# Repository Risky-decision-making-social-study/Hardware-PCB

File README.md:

# rpi-header-pcb

BOM: <https://risky-decision-making-social-study.github.io/Hardware-PCB/>

## Kicad project

The kicad project situated in the `monkey-rpi-header-pcb/` folder.

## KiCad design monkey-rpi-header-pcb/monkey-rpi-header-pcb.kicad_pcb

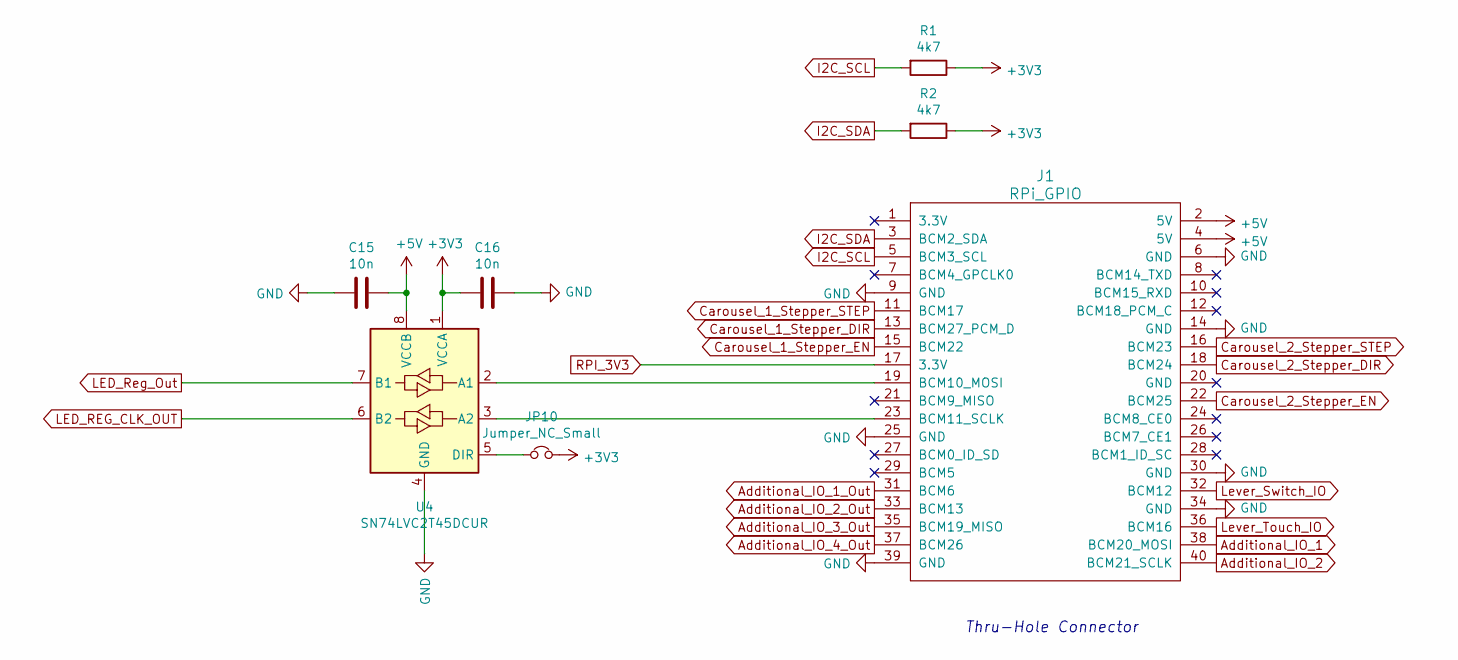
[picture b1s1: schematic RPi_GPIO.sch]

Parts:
C15, C16: 10n; C_0603_1608Metric; Part CL10B103KB8NNNC
J1: RPi_GPIO; Pin_Header_Straight_2x20; Part PRT-14017
JP10: Jumper_NC_Small; SolderJumper-2_P1.3mm_Bridged_RoundedPad1.0x1.5mm
R1, R2: 4k7; R_0805_2012Metric; Part CRCW08054K70FKEAC
U4: SN74LVC2T45DCUR; VSSOP-8_2.4x2.1mm_P0.5mm

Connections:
+5V: C15.1, J1.2 (5V), J1.4 (5V), U4.8 (VCCB); also elsewhere on the board
Additional_IO_1: J1.38 (BCM20_MOSI); also elsewhere on the board
Additional_IO_1_Out: J1.31 (BCM6); also elsewhere on the board
Additional_IO_2: J1.40 (BCM21_SCLK); also elsewhere on the board
Additional_IO_2_Out: J1.33 (BCM13); also elsewhere on the board
Additional_IO_3_Out: J1.35 (BCM19_MISO); also elsewhere on the board
Additional_IO_4_Out: J1.37 (BCM26); also elsewhere on the board
Carousel_1_Stepper_DIR: J1.13 (BCM27_PCM_D); also elsewhere on the board
Carousel_1_Stepper_EN: J1.15 (BCM22); also elsewhere on the board
Carousel_1_Stepper_STEP: J1.11 (BCM17); also elsewhere on the board
Carousel_2_Stepper_DIR: J1.18 (BCM24); also elsewhere on the board
Carousel_2_Stepper_EN: J1.22 (BCM25); also elsewhere on the board
Carousel_2_Stepper_STEP: J1.16 (BCM23); also elsewhere on the board
GND: C15.2, C16.1, J1.6 (GND), J1.9 (GND), J1.14 (GND), J1.25 (GND), J1.30 (GND), J1.34 (GND), J1.39 (GND), U4.4 (GND); also elsewhere on the board
I2C_SCL: J1.5 (BCM3_SCL), R1.2; also elsewhere on the board
I2C_SDA: J1.3 (BCM2_SDA), R2.2; also elsewhere on the board
LED_REG_CLK_OUT: U4.6 (B2); also elsewhere on the board
LED_Reg_Out: U4.7 (B1); also elsewhere on the board
Lever_Switch_IO: J1.32 (BCM12); also elsewhere on the board
Lever_Touch_IO: J1.36 (BCM16); also elsewhere on the board
unnamed: J1.19 (BCM10_MOSI), U4.2 (A1)
unnamed: J1.23 (BCM11_SCLK), U4.3 (A2)
unnamed: JP10.1, U4.5 (DIR)
RPI_3V3: J1.17 (3.3V); also elsewhere on the board

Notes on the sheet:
Thru-Hole Connector

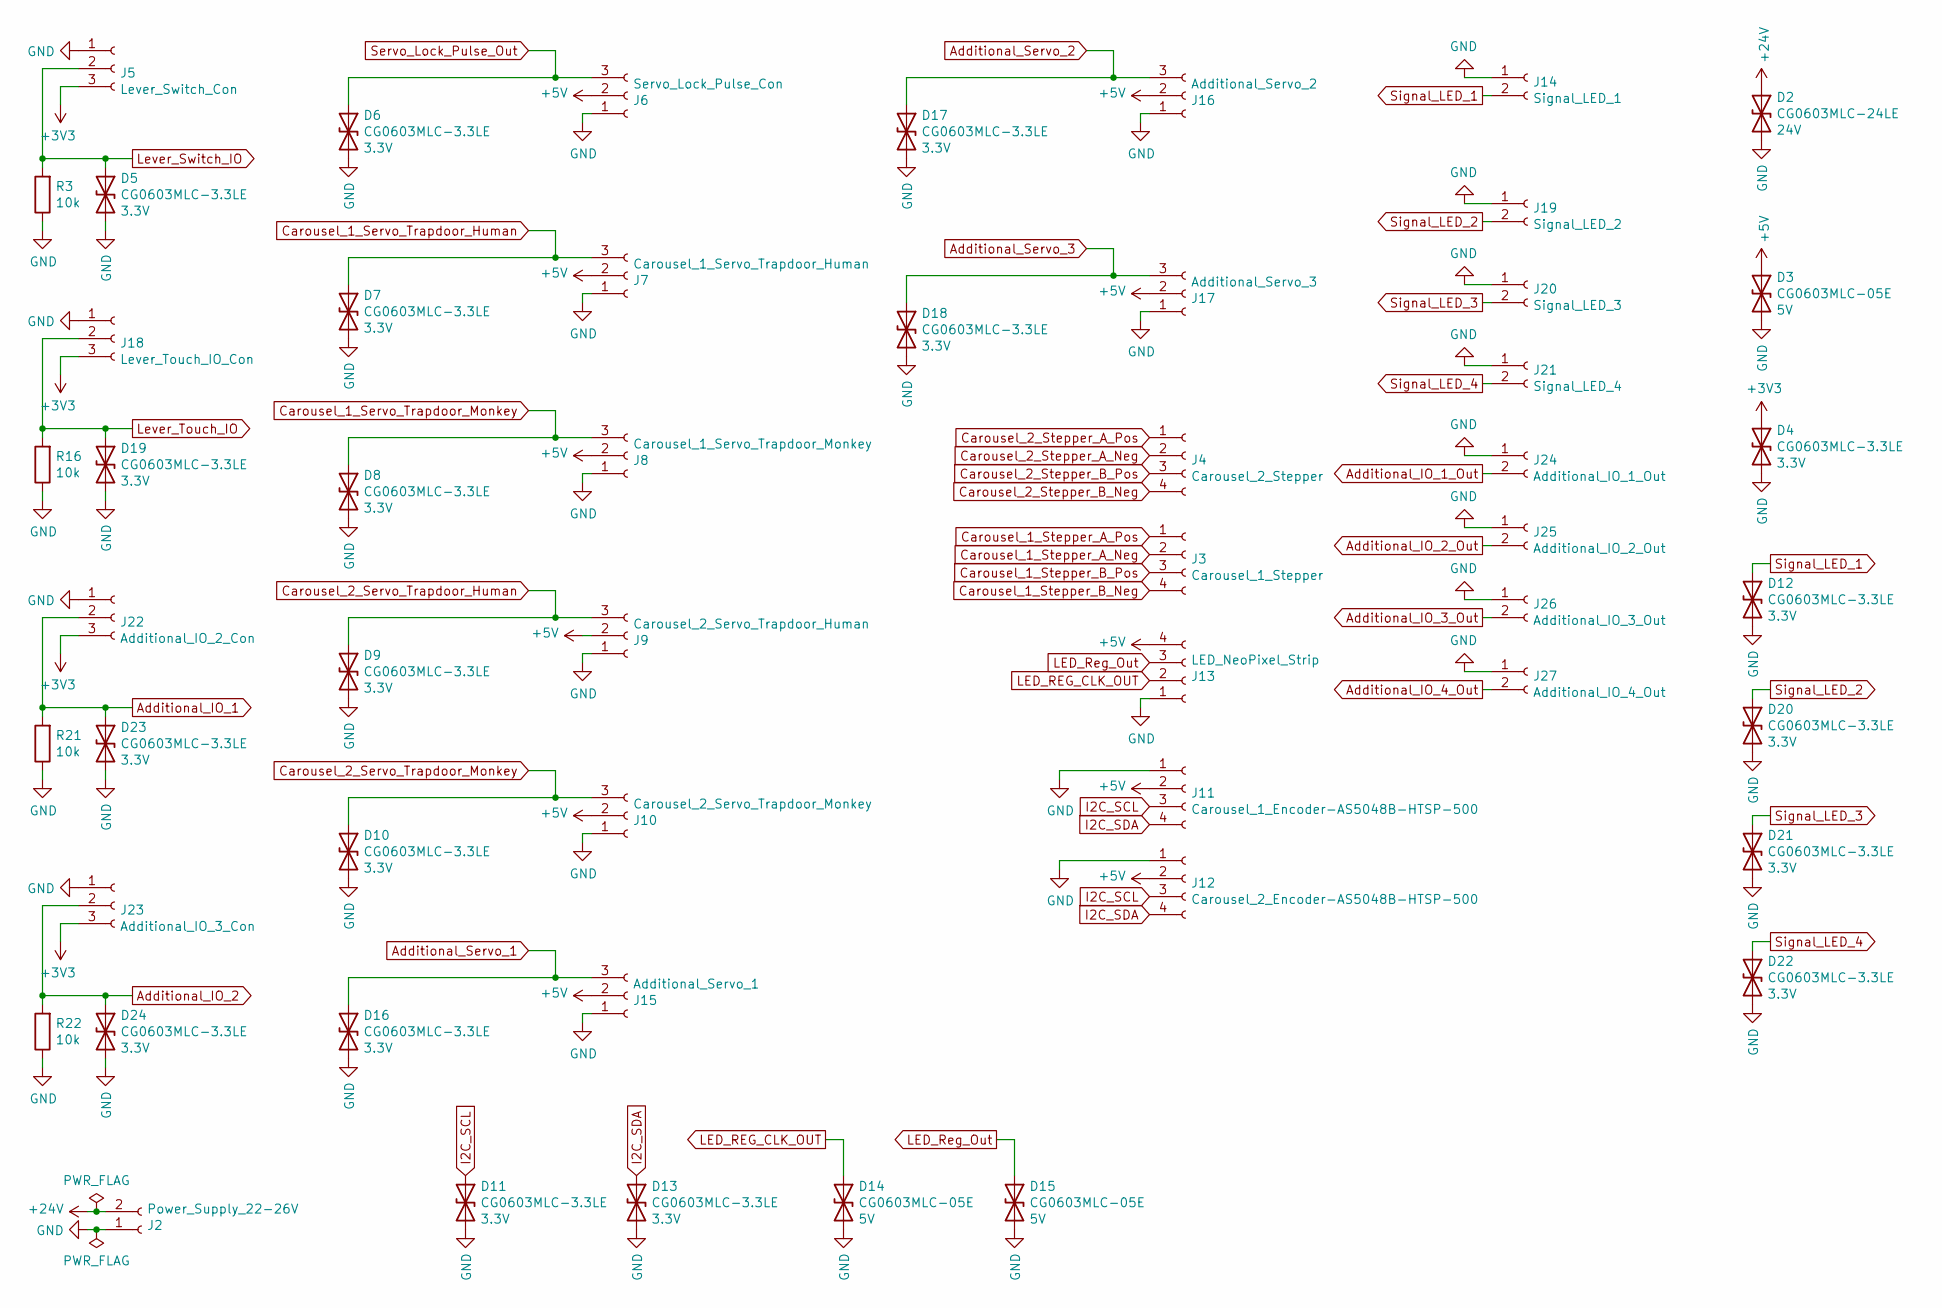
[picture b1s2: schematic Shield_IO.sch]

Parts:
D2: CG0603MLC-24LE; D_0603_1608Metric; Part CG0603MLC-24LE
D3, D14, D15: CG0603MLC-05E; D_0603_1608Metric; Part CG0603MLC-05E
D4, D5, D6, D7, D8, D9, D10, D11, D12, D13, D16, D17, D18, D19, D20, D21, D22, D23, D24: CG0603MLC-3.3LE; D_0603_1608Metric; Part CG0603MLC-3.3LE
J2: Power_Supply_22-26V; PhoenixContact_MC_1,5_2-G-3.81_1x02_P3.81mm_Horizontal; Part 1803277 und 1803578
J3: Carousel_1_Stepper; PinHeader_1x04_P2.54mm_Vertical
J4: Carousel_2_Stepper; PinHeader_1x04_P2.54mm_Vertical
J5: Lever_Switch_Con; PinHeader_1x03_P2.54mm_Vertical; Part PPTC021LFBN-RC
J6: Servo_Lock_Pulse_Con; PinHeader_1x03_P2.54mm_Vertical
J7: Carousel_1_Servo_Trapdoor_Human; PinHeader_1x03_P2.54mm_Vertical
J8: Carousel_1_Servo_Trapdoor_Monkey; PinHeader_1x03_P2.54mm_Vertical
J9: Carousel_2_Servo_Trapdoor_Human; PinHeader_1x03_P2.54mm_Vertical
J10: Carousel_2_Servo_Trapdoor_Monkey; PinHeader_1x03_P2.54mm_Vertical
J11: Carousel_1_Encoder-AS5048B-HTSP-500; PinHeader_1x04_P2.54mm_Vertical
J12: Carousel_2_Encoder-AS5048B-HTSP-500; PinHeader_1x04_P2.54mm_Vertical
J13: LED_NeoPixel_Strip; PinHeader_1x04_P2.54mm_Vertical
J14: Signal_LED_1; PinHeader_1x02_P2.54mm_Vertical
J15: Additional_Servo_1; PinHeader_1x03_P2.54mm_Vertical
J16: Additional_Servo_2; PinHeader_1x03_P2.54mm_Vertical
J17: Additional_Servo_3; PinHeader_1x03_P2.54mm_Vertical
J18: Lever_Touch_IO_Con; PinHeader_1x03_P2.54mm_Vertical; Part PPTC021LFBN-RC
J19: Signal_LED_2; PinHeader_1x02_P2.54mm_Vertical
J20: Signal_LED_3; PinHeader_1x02_P2.54mm_Vertical
J21: Signal_LED_4; PinHeader_1x02_P2.54mm_Vertical
J22: Additional_IO_2_Con; PinHeader_1x03_P2.54mm_Vertical; Part PPTC021LFBN-RC
J23: Additional_IO_3_Con; PinHeader_1x03_P2.54mm_Vertical; Part PPTC021LFBN-RC
J24: Additional_IO_1_Out; PinHeader_1x02_P2.54mm_Vertical
J25: Additional_IO_2_Out; PinHeader_1x02_P2.54mm_Vertical
J26: Additional_IO_3_Out; PinHeader_1x02_P2.54mm_Vertical
J27: Additional_IO_4_Out; PinHeader_1x02_P2.54mm_Vertical
R3, R16, R21, R22: 10k; R_0805_2012Metric; Part CRCW080510K0FKEAC

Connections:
+5V: D3.1 (A1), J6.2, J7.2, J8.2, J9.2, J10.2, J11.2, J12.2, J13.4, J15.2, J16.2, J17.2; also elsewhere on the board
+24V: D2.1 (A1), J2.2; also elsewhere on the board
Additional_IO_1: D23.1 (A1), J22.2, R21.2; also elsewhere on the board
Additional_IO_1_Out: J24.2; also elsewhere on the board
Additional_IO_2: D24.1 (A1), J23.2, R22.2; also elsewhere on the board
Additional_IO_2_Out: J25.2; also elsewhere on the board
Additional_IO_3_Out: J26.2; also elsewhere on the board
Additional_IO_4_Out: J27.2; also elsewhere on the board
Additional_Servo_1: D16.1 (A1), J15.3; also elsewhere on the board
Additional_Servo_2: D17.1 (A1), J16.3; also elsewhere on the board
Additional_Servo_3: D18.1 (A1), J17.3; also elsewhere on the board
Carousel_1_Servo_Trapdoor_Human: D7.1 (A1), J7.3; also elsewhere on the board
Carousel_1_Servo_Trapdoor_Monkey: D8.1 (A1), J8.3; also elsewhere on the board
Carousel_1_Stepper_A_Neg: J3.2; also elsewhere on the board
Carousel_1_Stepper_A_Pos: J3.1; also elsewhere on the board
Carousel_1_Stepper_B_Neg: J3.4; also elsewhere on the board
Carousel_1_Stepper_B_Pos: J3.3; also elsewhere on the board
Carousel_2_Servo_Trapdoor_Human: D9.1 (A1), J9.3; also elsewhere on the board
Carousel_2_Servo_Trapdoor_Monkey: D10.1 (A1), J10.3; also elsewhere on the board
Carousel_2_Stepper_A_Neg: J4.2; also elsewhere on the board
Carousel_2_Stepper_A_Pos: J4.1; also elsewhere on the board
Carousel_2_Stepper_B_Neg: J4.4; also elsewhere on the board
Carousel_2_Stepper_B_Pos: J4.3; also elsewhere on the board
GND: D2.2 (A2), D3.2 (A2), D4.2 (A2), D5.2 (A2), D6.2 (A2), D7.2 (A2), D8.2 (A2), D9.2 (A2), D10.2 (A2), D11.2 (A2), D12.2 (A2), D13.2 (A2), D14.2 (A2), D15.2 (A2), D16.2 (A2), D17.2 (A2), D18.2 (A2), D19.2 (A2), D20.2 (A2), D21.2 (A2), D22.2 (A2), D23.2 (A2), D24.2 (A2), J2.1, J5.1, J6.1, J7.1, J8.1, J9.1, J10.1, J11.1, J12.1, J13.1, J14.1, J15.1, J16.1, J17.1, J18.1, J19.1, J20.1, J21.1, J22.1, J23.1, J24.1, J25.1, J26.1, J27.1, R3.1, R16.1, R21.1, R22.1; also elsewhere on the board
I2C_SCL: D11.1 (A1), J11.3, J12.3; also elsewhere on the board
I2C_SDA: D13.1 (A1), J11.4, J12.4; also elsewhere on the board
LED_REG_CLK_OUT: D14.1 (A1), J13.2; also elsewhere on the board
LED_Reg_Out: D15.1 (A1), J13.3; also elsewhere on the board
Lever_Switch_IO: D5.1 (A1), J5.2, R3.2; also elsewhere on the board
Lever_Touch_IO: D19.1 (A1), J18.2, R16.2; also elsewhere on the board
Servo_Lock_Pulse_Out: D6.1 (A1), J6.3; also elsewhere on the board
Signal_LED_1: D12.1 (A1), J14.2; also elsewhere on the board
Signal_LED_2: D20.1 (A1), J19.2; also elsewhere on the board
Signal_LED_3: D21.1 (A1), J20.2; also elsewhere on the board
Signal_LED_4: D22.1 (A1), J21.2; also elsewhere on the board

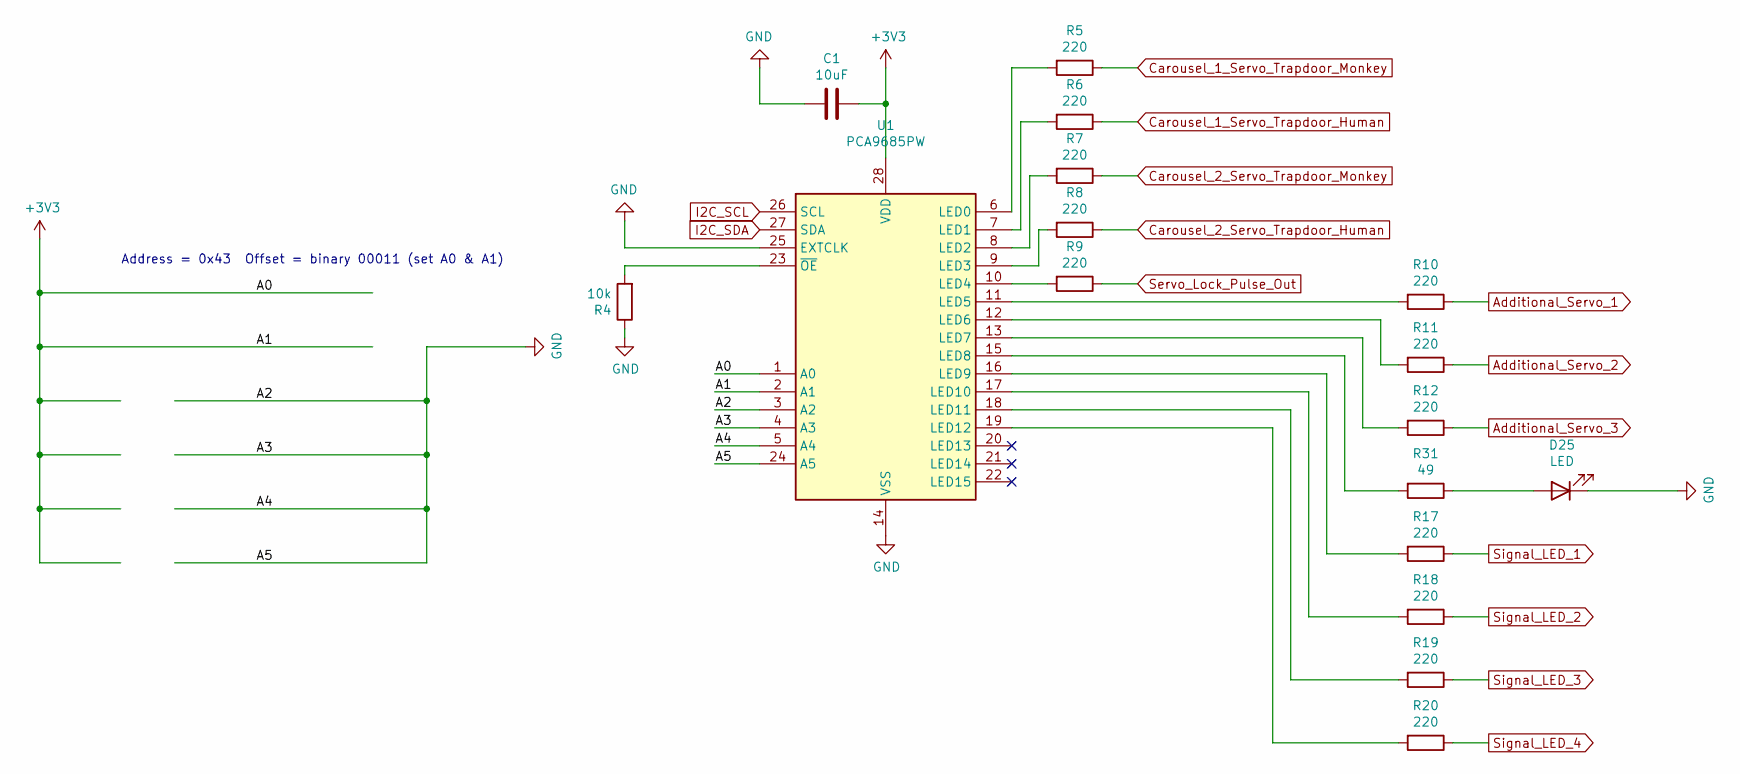
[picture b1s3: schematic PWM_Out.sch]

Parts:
C1: 10uF; C_0805_2012Metric; Part CL21A106KQCLRNC
D25: LED; LED_0805_2012Metric; Part 150080RS75000
R4: 10k; R_0805_2012Metric; Part CRCW080510K0FKEAC
R5, R6, R7, R8, R9, R10, R11, R12, R17, R18, R19, R20: 220; R_0805_2012Metric; Part CRCW0805220RFKEAC
R31: 49; R_0805_2012Metric; Part RC0805FR-0749R9L
U1: PCA9685PW; TSSOP-28_4.4x9.7mm_P0.65mm; Part PCA9685PW,118

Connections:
Additional_Servo_1: R10.1; also elsewhere on the board
Additional_Servo_2: R11.1; also elsewhere on the board
Additional_Servo_3: R12.1; also elsewhere on the board
Carousel_1_Servo_Trapdoor_Human: R6.1; also elsewhere on the board
Carousel_1_Servo_Trapdoor_Monkey: R5.1; also elsewhere on the board
Carousel_2_Servo_Trapdoor_Human: R8.1; also elsewhere on the board
Carousel_2_Servo_Trapdoor_Monkey: R7.1; also elsewhere on the board
GND: C1.2, D25.1 (K), R4.1, U1.3 (A2), U1.4 (A3), U1.5 (A4), U1.14 (VSS), U1.24 (A5), U1.25 (EXTCLK); also elsewhere on the board
I2C_SCL: U1.26 (SCL); also elsewhere on the board
I2C_SDA: U1.27 (SDA); also elsewhere on the board
unnamed: D25.2 (A), R31.1
unnamed: R4.2, U1.23 (~OE)
unnamed: R5.2, U1.6 (LED0)
unnamed: R6.2, U1.7 (LED1)
unnamed: R7.2, U1.8 (LED2)
unnamed: R8.2, U1.9 (LED3)
unnamed: R9.2, U1.10 (LED4)
unnamed: R10.2, U1.11 (LED5)
unnamed: R11.2, U1.12 (LED6)
unnamed: R12.2, U1.13 (LED7)
unnamed: R17.2, U1.16 (LED9)
unnamed: R18.2, U1.17 (LED10)
unnamed: R19.2, U1.18 (LED11)
unnamed: R20.2, U1.19 (LED12)
unnamed: R31.2, U1.15 (LED8)
Servo_Lock_Pulse_Out: R9.1; also elsewhere on the board
Signal_LED_1: R17.1; also elsewhere on the board
Signal_LED_2: R18.1; also elsewhere on the board
Signal_LED_3: R19.1; also elsewhere on the board
Signal_LED_4: R20.1; also elsewhere on the board

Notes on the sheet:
Address = 0x43 Offset = binary 00011 (set A0 & A1)

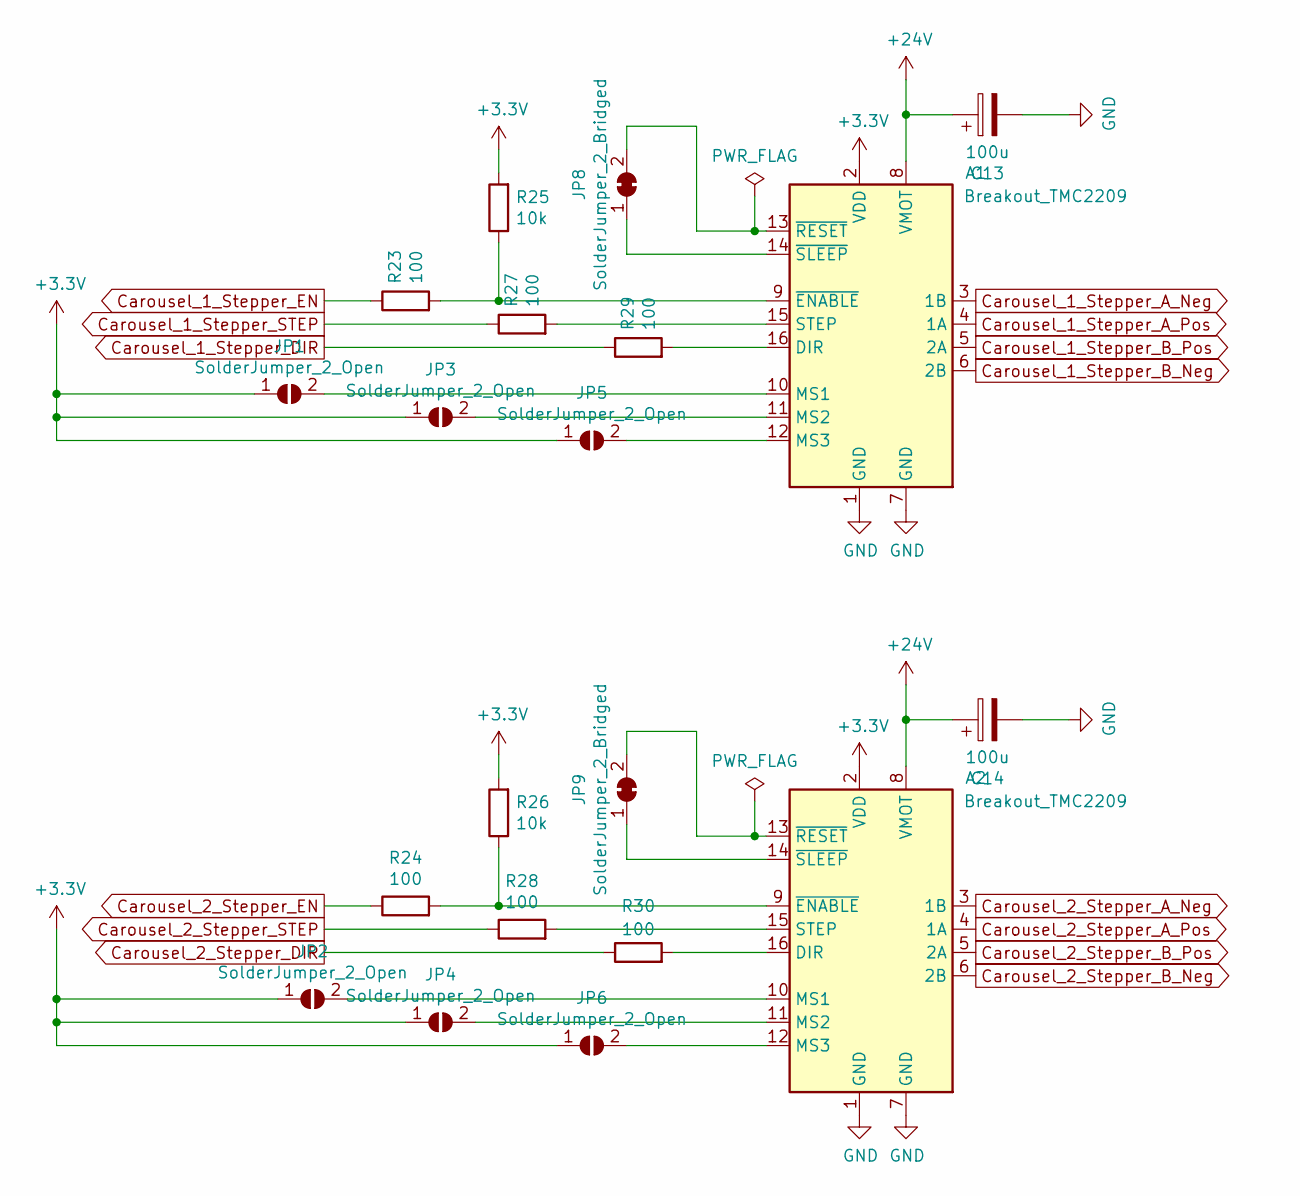
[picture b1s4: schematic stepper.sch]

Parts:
A1, A2: Breakout_TMC2209; Pololu_Breakout-16_15.2x20.3mm
C13, C14: 100u; CP_Elec_6.3x7.7; Part EEE-FT1V101AP
JP1, JP2, JP3, JP4, JP5, JP6: SolderJumper_2_Open; SolderJumper-2_P1.3mm_Open_RoundedPad1.0x1.5mm
JP8, JP9: SolderJumper_2_Bridged; SolderJumper-2_P1.3mm_Bridged_RoundedPad1.0x1.5mm
R23, R24, R27, R28, R29, R30: 100; R_0603_1608Metric; Part CRCW0603100RFKEAC
R25, R26: 10k; R_0805_2012Metric; Part CRCW080510K0FKEAC

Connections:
+24V: A1.8 (VMOT), A2.8 (VMOT), C13.1, C14.1; also elsewhere on the board
Carousel_1_Stepper_A_Neg: A1.3 (1B); also elsewhere on the board
Carousel_1_Stepper_A_Pos: A1.4 (1A); also elsewhere on the board
Carousel_1_Stepper_B_Neg: A1.6 (2B); also elsewhere on the board
Carousel_1_Stepper_B_Pos: A1.5 (2A); also elsewhere on the board
Carousel_1_Stepper_DIR: R29.1; also elsewhere on the board
Carousel_1_Stepper_EN: R23.1; also elsewhere on the board
Carousel_1_Stepper_STEP: R27.1; also elsewhere on the board
Carousel_2_Stepper_A_Neg: A2.3 (1B); also elsewhere on the board
Carousel_2_Stepper_A_Pos: A2.4 (1A); also elsewhere on the board
Carousel_2_Stepper_B_Neg: A2.6 (2B); also elsewhere on the board
Carousel_2_Stepper_B_Pos: A2.5 (2A); also elsewhere on the board
Carousel_2_Stepper_DIR: R30.1; also elsewhere on the board
Carousel_2_Stepper_EN: R24.1; also elsewhere on the board
Carousel_2_Stepper_STEP: R28.1; also elsewhere on the board
GND: A1.1 (GND), A1.7 (GND), A2.1 (GND), A2.7 (GND), C13.2, C14.2; also elsewhere on the board
unnamed: A1.9 (~ENABLE), R23.2, R25.1
unnamed: A1.10 (MS1), JP1.2 (B)
unnamed: A1.11 (MS2), JP3.2 (B)
unnamed: A1.12 (MS3), JP5.2 (B)
unnamed: A1.13 (~RESET), JP8.2 (B)
unnamed: A1.14 (~SLEEP), JP8.1 (A)
unnamed: A1.15 (STEP), R27.2
unnamed: A1.16 (DIR), R29.2
unnamed: A2.9 (~ENABLE), R24.2, R26.1
unnamed: A2.10 (MS1), JP2.2 (B)
unnamed: A2.11 (MS2), JP4.2 (B)
unnamed: A2.12 (MS3), JP6.2 (B)
unnamed: A2.13 (~RESET), JP9.2 (B)
unnamed: A2.14 (~SLEEP), JP9.1 (A)
unnamed: A2.15 (STEP), R28.2
unnamed: A2.16 (DIR), R30.2

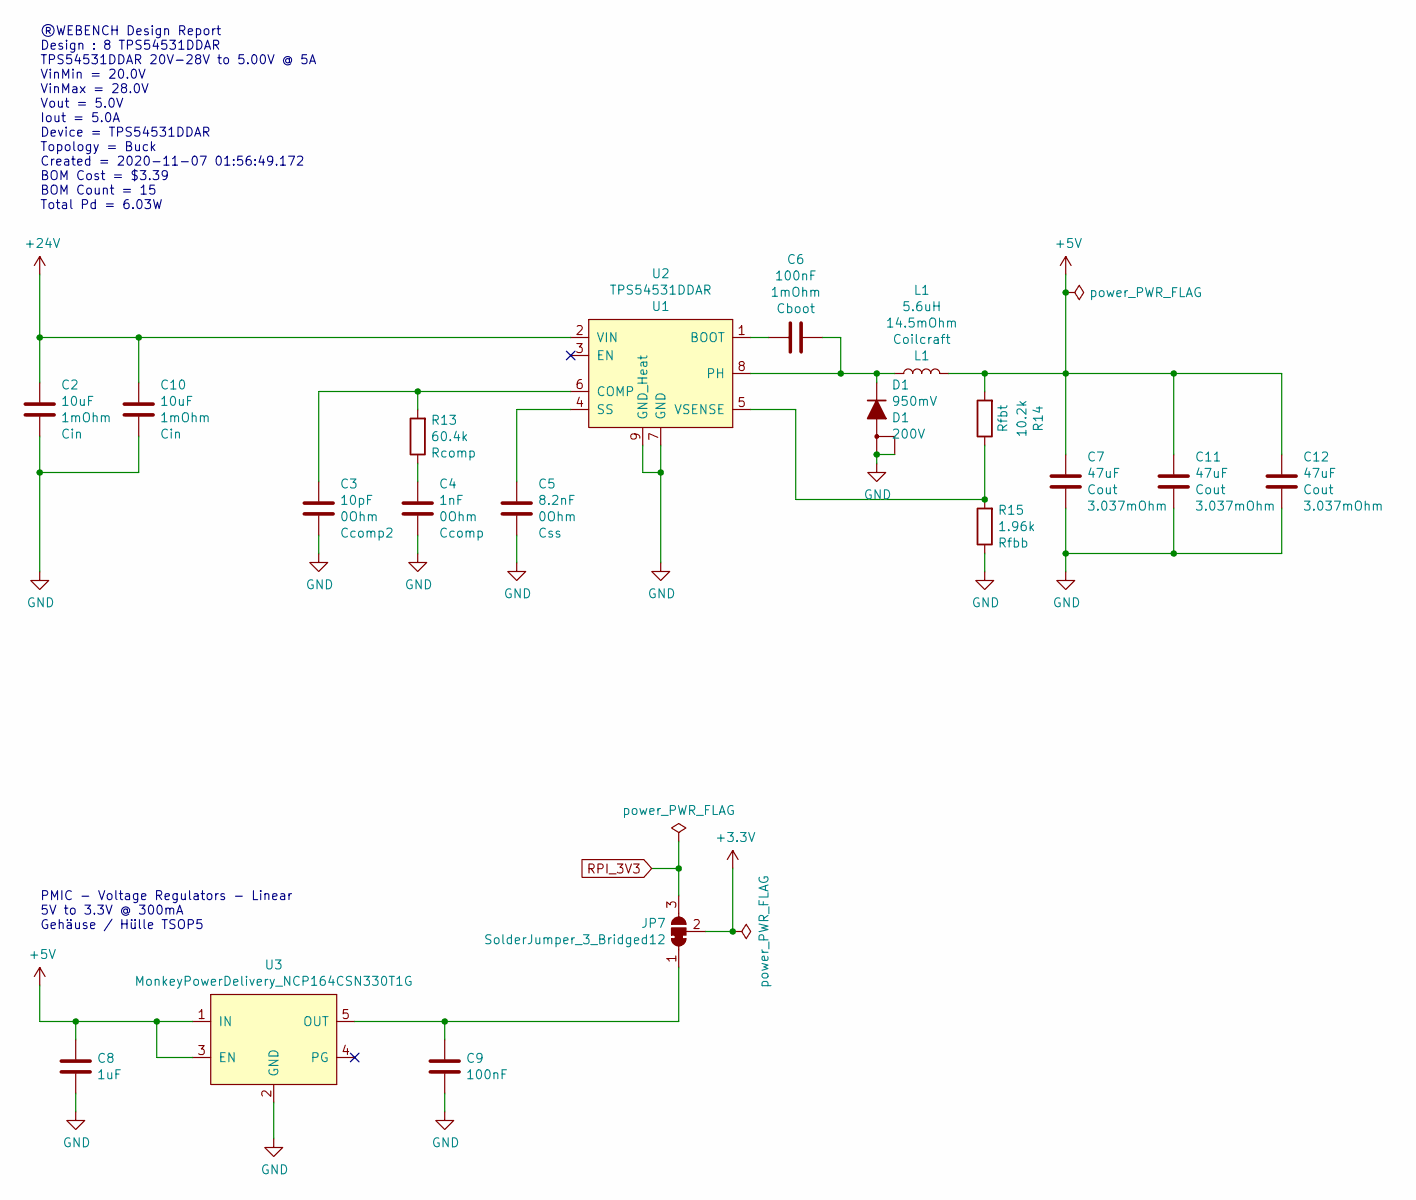
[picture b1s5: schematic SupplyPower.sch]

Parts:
C2, C10: 10uF; C_1210_3225Metric; Part C3225X7R1H106M250AC
C3: 10pF; C_0805_2012Metric; Part CL21C100JBANNNC
C4: 1nF; C_0805_2012Metric; Part GRM2165C1H102JA01J
C5: 8.2nF; C_1206_3216Metric; Part 12063A822JAT2A
C6, C9: 100nF; C_0805_2012Metric; Part CC0805KRX7R7BB104
C7, C11, C12: 47uF; C_1210_3225Metric; Part GRM32ER61C476KE15L
C8: 1uF; C_0805_2012Metric; Part CL21B105KOFNNNG
D1: 950mV; TO-252-2; Part SBRD10200TR
JP7: SolderJumper_3_Bridged12; SolderJumper-3_P1.3mm_Bridged12_RoundedPad1.0x1.5mm_NumberL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
L1: 5.6uH; XAL6060562MEB; Part XAL6060-562MEB
R13: 60.4k; R_0805_2012Metric; Part CRCW080560K4FKEA
R14: 10.2k; R_0805_2012Metric; Part CRCW080510K2FKEA
R15: 1.96k; R_0805_2012Metric; Part CRCW08051K96FKEA
U2: TPS54531DDAR; Texas_HSOP-8-1EP_3.9x4.9mm_P1.27mm_ThermalVias; Part TPS54531DDAR
U3: MonkeyPowerDelivery_NCP164CSN330T1G; TSOP-5_1.65x3.05mm_P0.95mm; Part NCP164CSN330T1G

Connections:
+5V: C7.2, C8.1, C11.2, C12.2, L1.2, R14.2, U3.1 (IN), U3.3 (EN); also elsewhere on the board
+24V: C2.2, C10.2, U2.2 (VIN); also elsewhere on the board
GND: C2.1, C3.1, C4.1, C5.1, C7.1, C8.2, C9.2, C10.1, C11.1, C12.1, D1.1 (A1), D1.3 (A2), R15.1, U2.7 (GND), U2.9 (GND_Heat), U3.2 (GND); also elsewhere on the board
unnamed: C3.2, R13.2, U2.6 (COMP)
unnamed: C4.2, R13.1
unnamed: C5.2, U2.4 (SS)
unnamed: C6.1, D1.2 (K), L1.1, U2.8 (PH)
unnamed: C6.2, U2.1 (BOOT)
unnamed: C9.1, JP7.1 (A), U3.5 (OUT)
unnamed: R14.1, R15.2, U2.5 (VSENSE)
RPI_3V3: JP7.3 (B); also elsewhere on the board

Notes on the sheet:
®WEBENCH Design Report Design : 8 TPS54531DDAR TPS54531DDAR 20V-28V to 5.00V @ 5A VinMin = 20.0V VinMax = 28.0V Vout = 5.0V Iout = 5.0A Device = TPS54531DDAR Topology = Buck Created = 2020-11-07 01:56:49.172 BOM Cost = $3.39 BOM Count = 15 Total Pd = 6.03W
PMIC - Voltage Regulators - Linear 5V to 3.3V @ 300mA Gehäuse / Hülle TSOP5

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
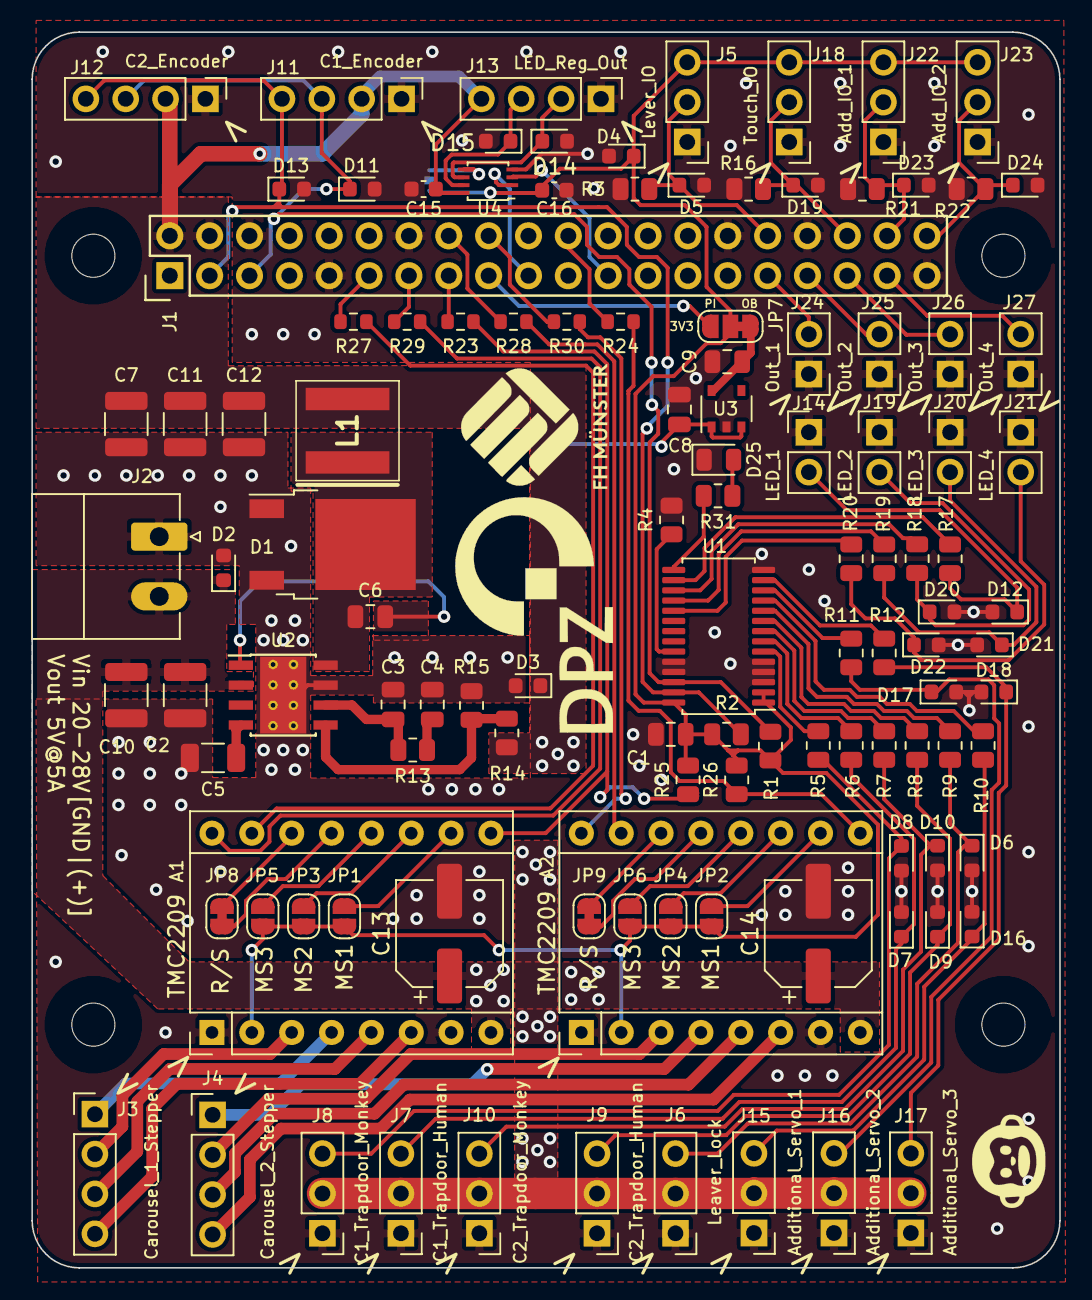
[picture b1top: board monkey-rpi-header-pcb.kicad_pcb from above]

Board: 2 copper layers, 65.5 x 78.8 mm, 119 parts (1 on the bottom side), 84 nets.

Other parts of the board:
Ref**: Val**; monkey-drawing
Ref**#2: Val**; FH_silk
Ref**#3: Val**; DPZ_SilkS

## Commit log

2023-11-08 upload files
